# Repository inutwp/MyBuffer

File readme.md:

## MyBuffer

Collection Discrete/Opamp Buffer Module.

- 4x Opamp Buffer
- Diamond Buffer
- Eaton Buffer
- Diamond Buffer with LM317

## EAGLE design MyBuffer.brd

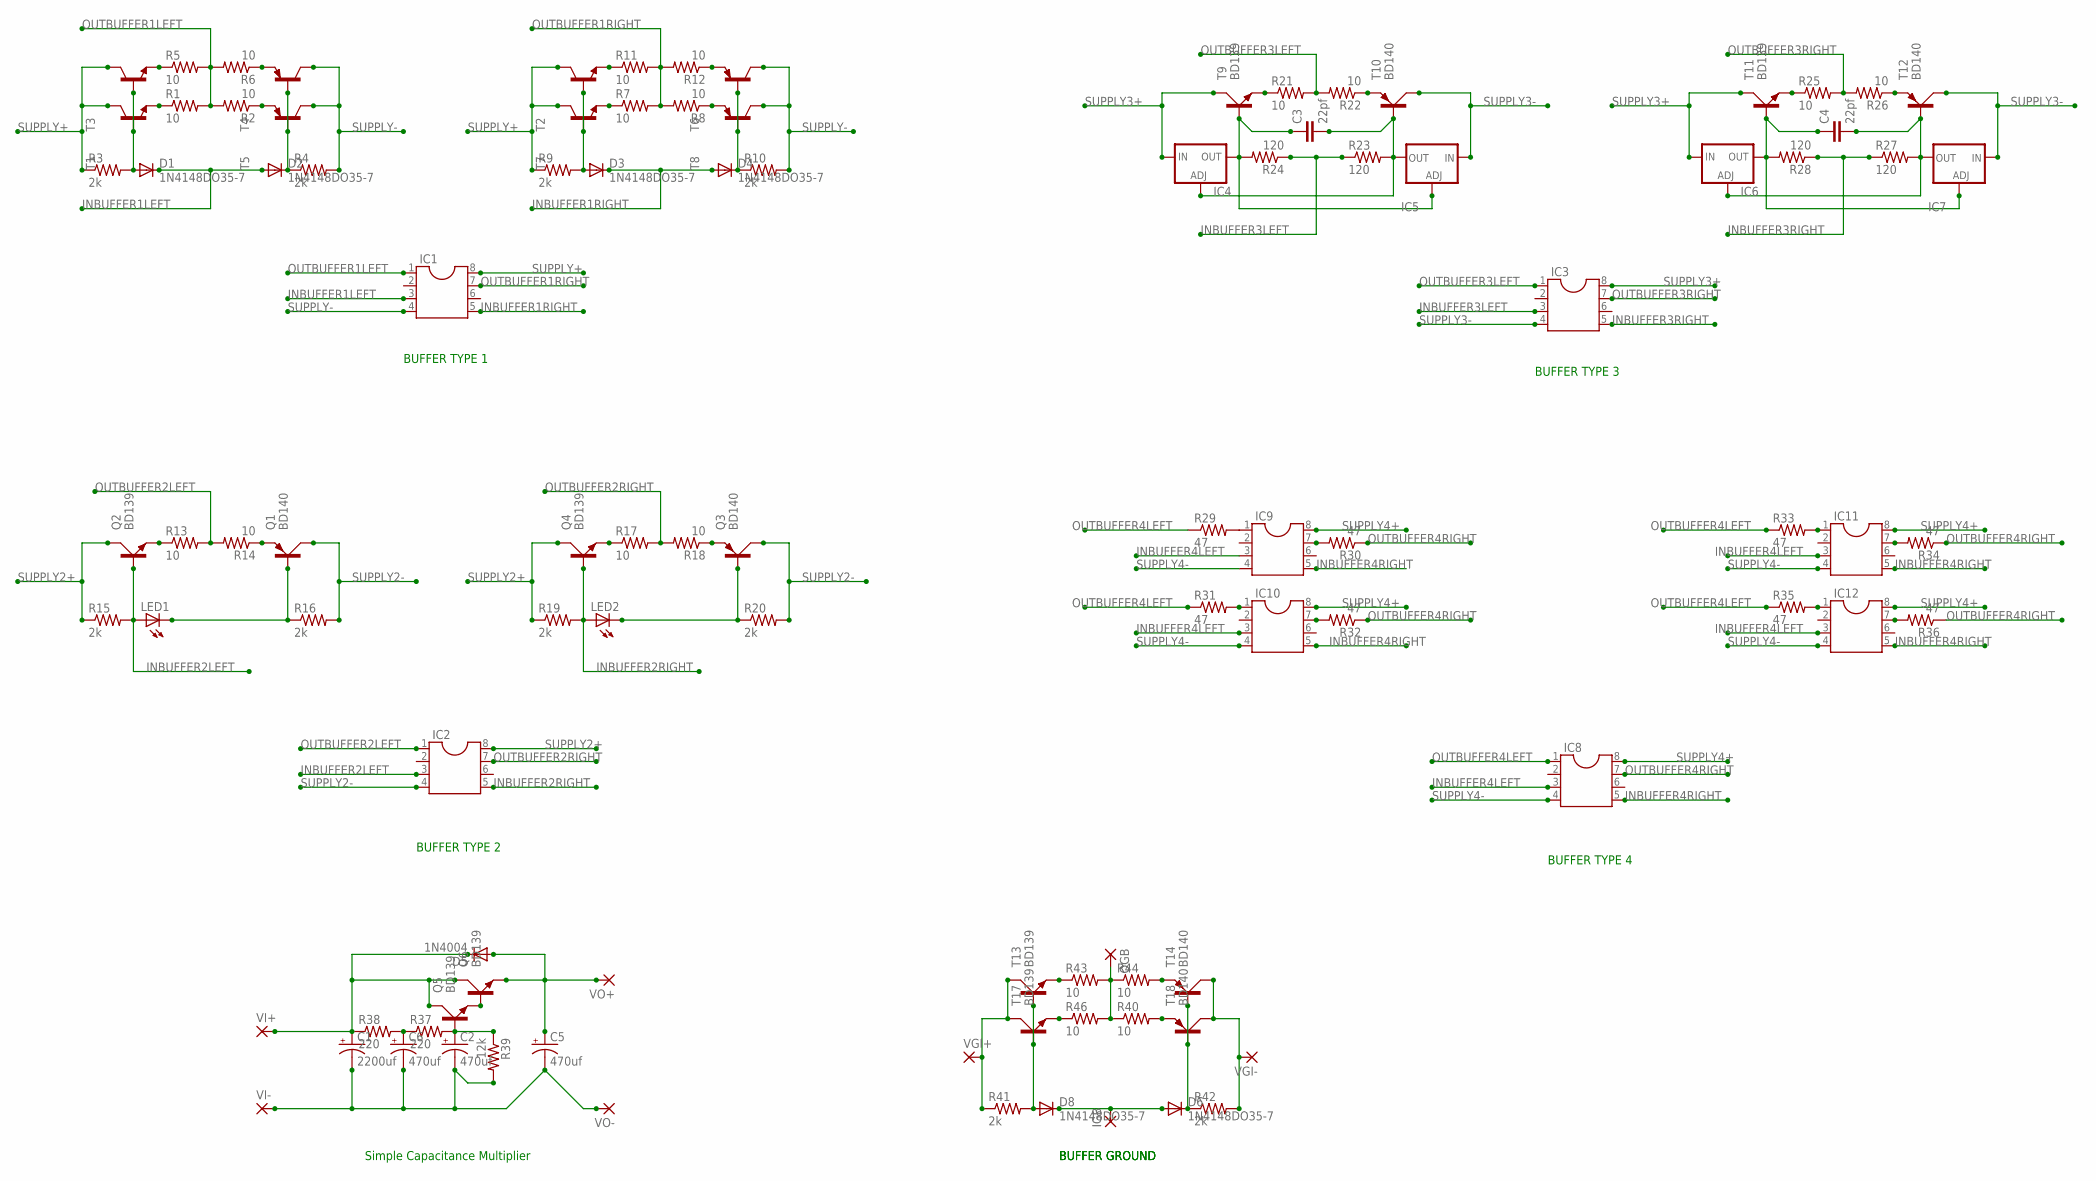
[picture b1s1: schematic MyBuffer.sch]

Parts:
C1: 2200uf; E7,5-16
C2, C5, C6: 470uf; E7,5-16
C3, C4: 22pf; C5B2.5
D1, D2, D3, D4, D6, D8: 1N4148DO35-7; DO35-7
D5: 1N4004; DO41-10
IC1, IC2, IC3, IC8, IC9, IC10, IC11, IC12: DIL8; DIL08
IC4, IC6: LM317TS; 317TS
IC5, IC7: LM337TS; 337TS
IGB: 2,54/0,8
LED1, LED2: LED3MM
OGB: 2,54/0,8
Q1, Q3: BD140; TO126AV
Q2, Q4, Q5, Q6: BD139; TO126AV
R1, R2, R7, R8, R13, R14, R17, R18, R21, R22, R25, R26, R40, R43, R44, R46: 10; 0207/10
R3, R4, R9, R10, R15, R16, R19, R20, R41, R42: 2k; 0207/10
R5, R6, R11, R12: 10; 0207/2V
R23, R24, R27, R28: 120; 0207/10
R29, R30, R31, R32, R33, R34, R35, R36: 47; 0207/10
R37, R38: 220; 0207/10
R39: 12k; 0207/10
T1, T2, T3, T7: 29-NPN-TO92-EBC; TO92-EBC
T4, T5, T6, T8: 2N5401-PNP-TO92-EBC; TO92-EBC
T9, T11, T13, T17: BD139; TO126AV
T10, T12, T14, T18: BD140; TO126AV
VGI+: 2,54/0,8
VGI-: 2,54/0,8
VI+: 2,54/0,8
VI-: 2,54/0,8
VO+: 2,54/0,8
VO-: 2,54/0,8

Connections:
INBUFFER1LEFT: D1.C, D2.A, IC1.3
INBUFFER1RIGHT: D3.C, D4.A, IC1.5
INBUFFER2LEFT: IC2.3, LED1.A, Q2.B, R15.2
INBUFFER2RIGHT: IC2.5, LED2.A, Q4.B, R19.2
INBUFFER3LEFT: IC3.3, R23.1, R24.1
INBUFFER3RIGHT: IC3.5, R27.1, R28.1
INBUFFER4LEFT: IC8.3, IC9.3, IC10.3, IC11.3, IC12.3
INBUFFER4RIGHT: IC8.5, IC9.5, IC10.5, IC11.5, IC12.5
unnamed: R1.1, T1.E
unnamed: R2.1, T5.E
unnamed: D3.A, R9.2, T2.B, T7.B
unnamed: D1.A, R3.2, T1.B, T3.B
unnamed: D2.C, R4.1, T4.B, T5.B
unnamed: R6.1, T4.E
unnamed: R5.1, T3.E
unnamed: D4.C, R10.1, T6.B, T8.B
unnamed: R7.1, T7.E
unnamed: R8.1, T8.E
unnamed: R11.1, T2.E
unnamed: R12.1, T6.E
unnamed: Q2.E, R13.1
unnamed: Q4.E, R17.1
unnamed: Q1.E, R14.1
unnamed: Q3.E, R18.1
unnamed: LED2.K (C), Q3.B, R20.1
unnamed: LED1.K (C), Q1.B, R16.1
unnamed: R21.1, T9.E
unnamed: R22.1, T10.E
unnamed: C4.1, IC6.2 (OUT), IC7.1 (ADJ), R28.2, T11.B
unnamed: C3.1, IC4.2 (OUT), IC5.1 (ADJ), R24.2, T9.B
unnamed: C3.2, IC4.1 (ADJ), IC5.3 (OUT), R23.2, T10.B
unnamed: C4.2, IC6.1 (ADJ), IC7.3 (OUT), R27.2, T12.B
unnamed: R25.1, T11.E
unnamed: R26.1, T12.E
unnamed: IC9.1, R29.2
unnamed: C2.+, Q5.B, R37.2, R39.1
unnamed: Q5.E, Q6.B
unnamed: IC9.7, R30.2
unnamed: C6.+, R37.1, R38.2
unnamed: C1.+, D5.C, Q5.C, Q6.C, R38.1, VI+.1
unnamed: C1.-, C2.-, C5.-, C6.-, R39.2, VI-.1, VO-.1
unnamed: IC10.1, R31.2
unnamed: C5.+, D5.A, Q6.E, VO+.1
unnamed: OGB.1, R40.1, R43.2, R44.1, R46.2
unnamed: IC10.7, R32.2
unnamed: R46.1, T17.E
unnamed: IC11.1, R33.2
unnamed: R40.2, T18.E
unnamed: D6.C, R42.1, T14.B, T18.B
unnamed: D8.A, R41.2, T13.B, T17.B
unnamed: IC11.7, R34.2
unnamed: R41.1, T13.C, T17.C, VGI+.1
unnamed: IC12.1, R35.2
unnamed: R42.2, T14.C, T18.C, VGI-.1
unnamed: D6.A, D8.C, IGB.1
unnamed: R43.1, T13.E
unnamed: IC12.7, R36.2
unnamed: R44.2, T14.E
OUTBUFFER1LEFT: IC1.1, R1.2, R2.2, R5.2, R6.2
OUTBUFFER1RIGHT: IC1.7, R7.2, R8.2, R11.2, R12.2
OUTBUFFER2LEFT: IC2.1, R13.2, R14.2
OUTBUFFER2RIGHT: IC2.7, R17.2, R18.2
OUTBUFFER3LEFT: IC3.1, R21.2, R22.2
OUTBUFFER3RIGHT: IC3.7, R25.2, R26.2
OUTBUFFER4LEFT: IC8.1, R29.1, R31.1, R33.1, R35.1
OUTBUFFER4RIGHT: IC8.7, R30.1, R32.1, R34.1, R36.1
SUPPLY2+: IC2.8, Q2.C, Q4.C, R15.1, R19.1
SUPPLY2-: IC2.4, Q1.C, Q3.C, R16.2, R20.2
SUPPLY3+: IC3.8, IC4.3 (IN), IC6.3 (IN), T9.C, T11.C
SUPPLY3-: IC3.4, IC5.2 (IN), IC7.2 (IN), T10.C, T12.C
SUPPLY4+: IC8.8, IC9.8, IC10.8, IC11.8, IC12.8
SUPPLY4-: IC8.4, IC9.4, IC10.4, IC11.4, IC12.4
SUPPLY+: IC1.8, R3.1, R9.1, T1.C, T2.C, T3.C, T7.C
SUPPLY-: IC1.4, R4.2, R10.2, T4.C, T5.C, T6.C, T8.C

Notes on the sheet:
BUFFER TYPE 1
BUFFER TYPE 2
BUFFER TYPE 3
BUFFER TYPE 4
BUFFER GROUND
Simple Capacitance Multiplier

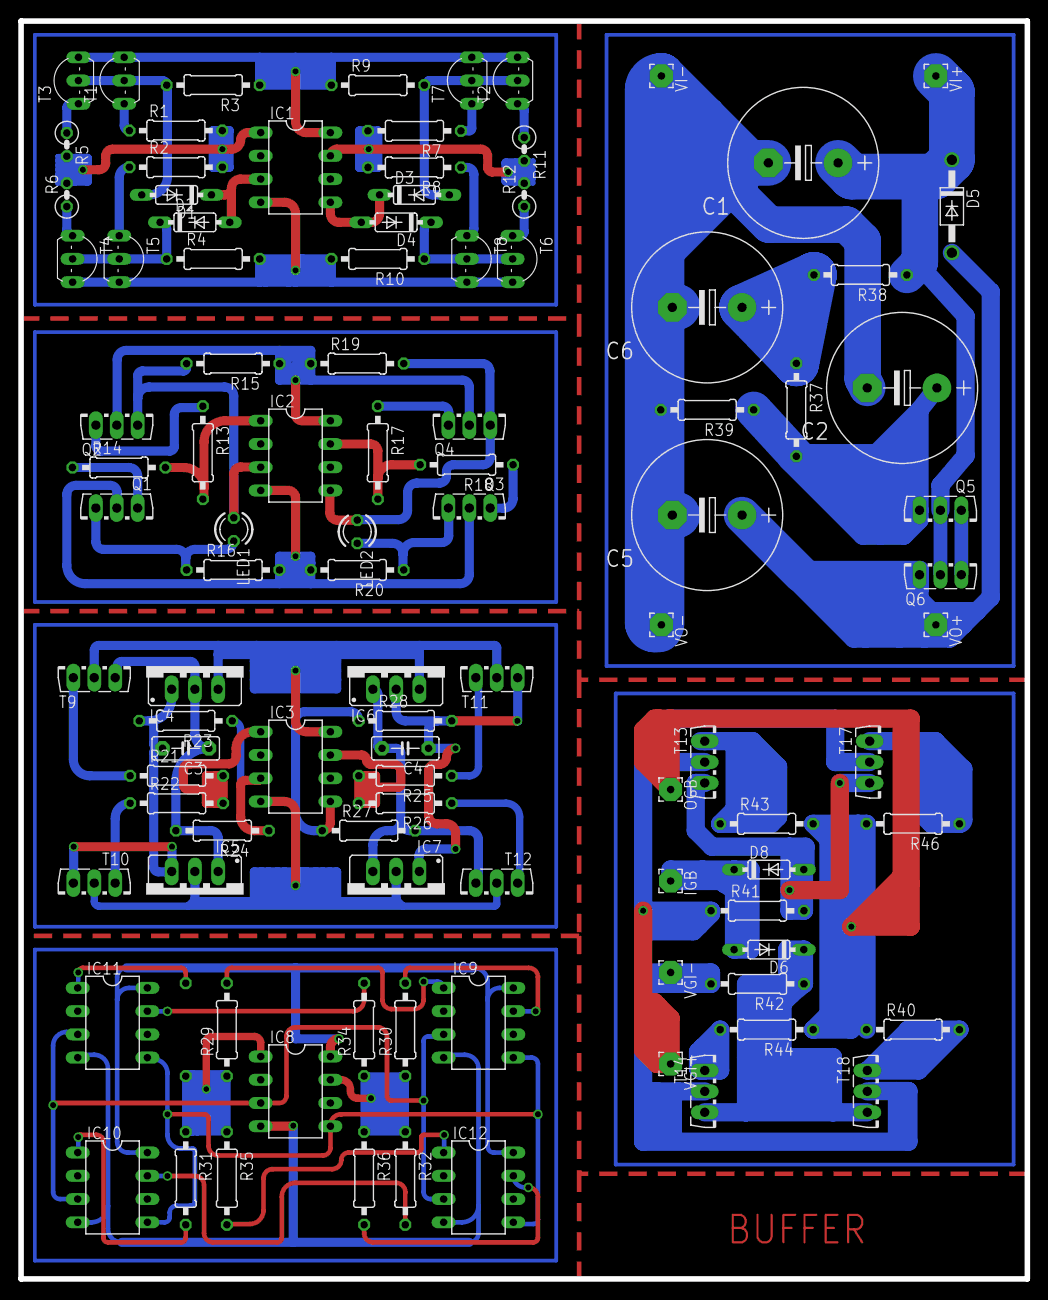
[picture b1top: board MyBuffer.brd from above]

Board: 2 copper layers, 110.0 x 137.5 mm, 102 parts (1 on the bottom side), 74 nets.

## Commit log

2020-06-14 edit wire width and via
2020-06-27 add module capacitance multiplier and buffer ground
